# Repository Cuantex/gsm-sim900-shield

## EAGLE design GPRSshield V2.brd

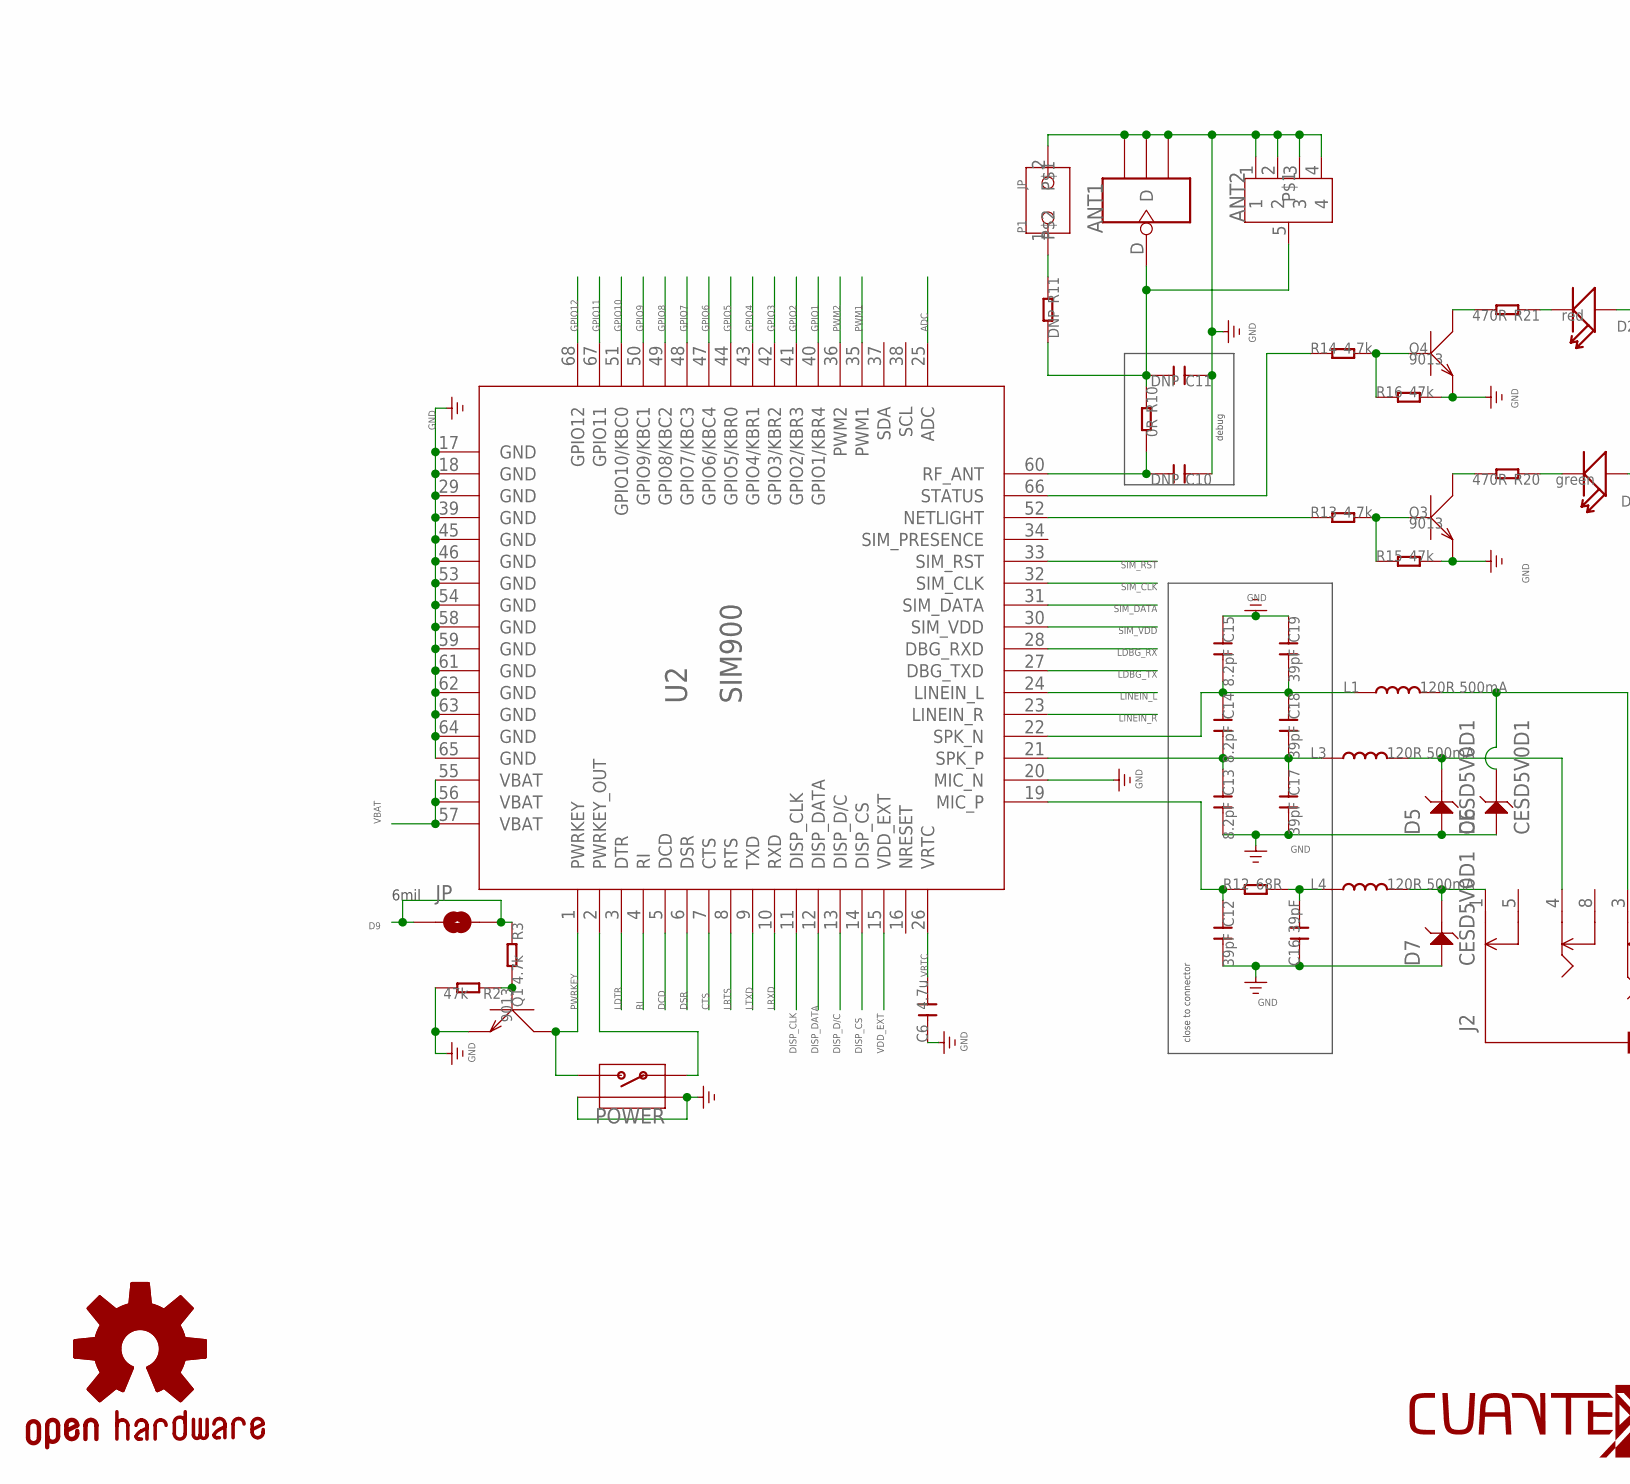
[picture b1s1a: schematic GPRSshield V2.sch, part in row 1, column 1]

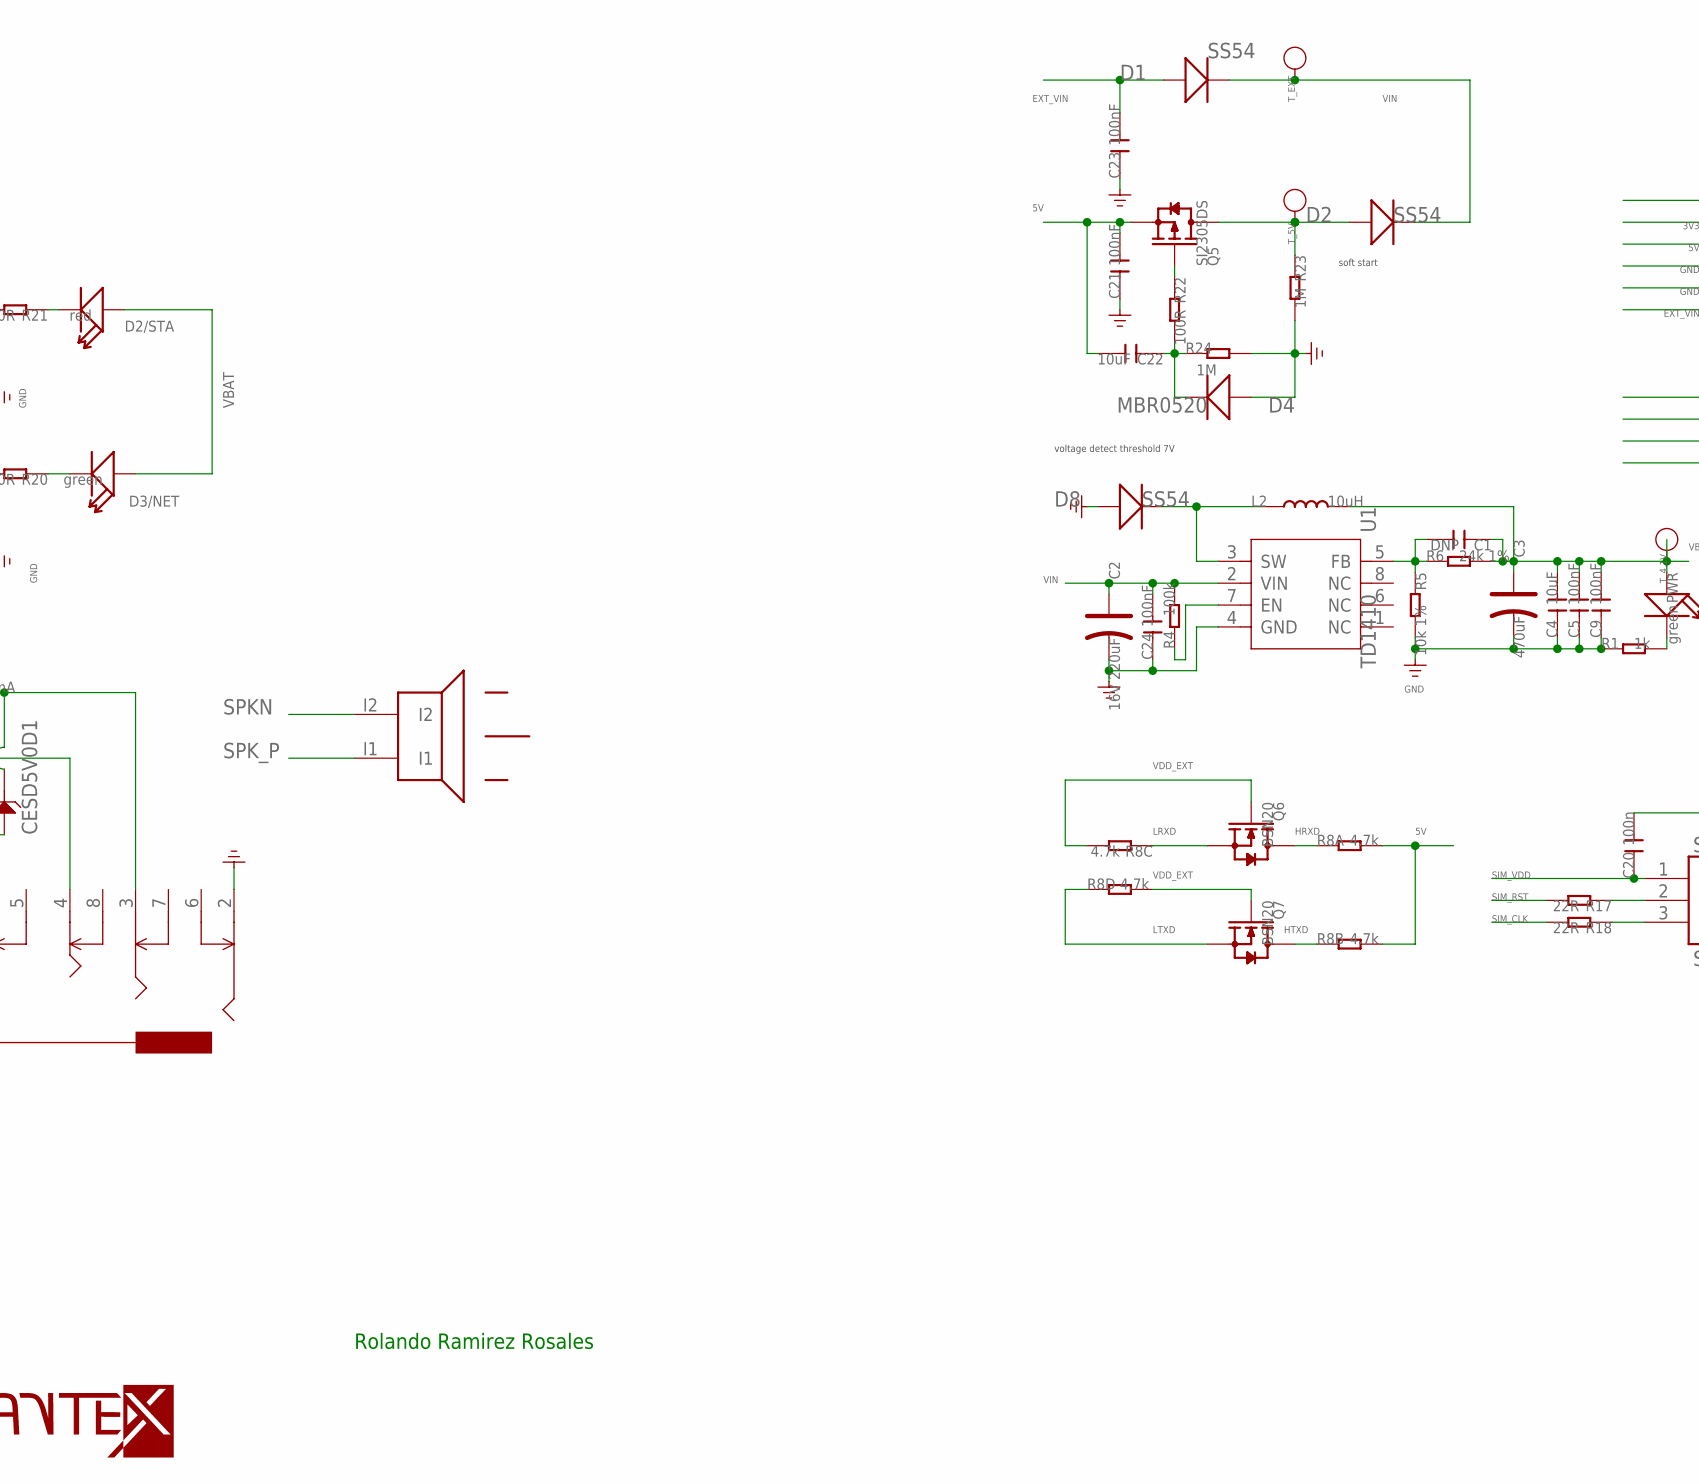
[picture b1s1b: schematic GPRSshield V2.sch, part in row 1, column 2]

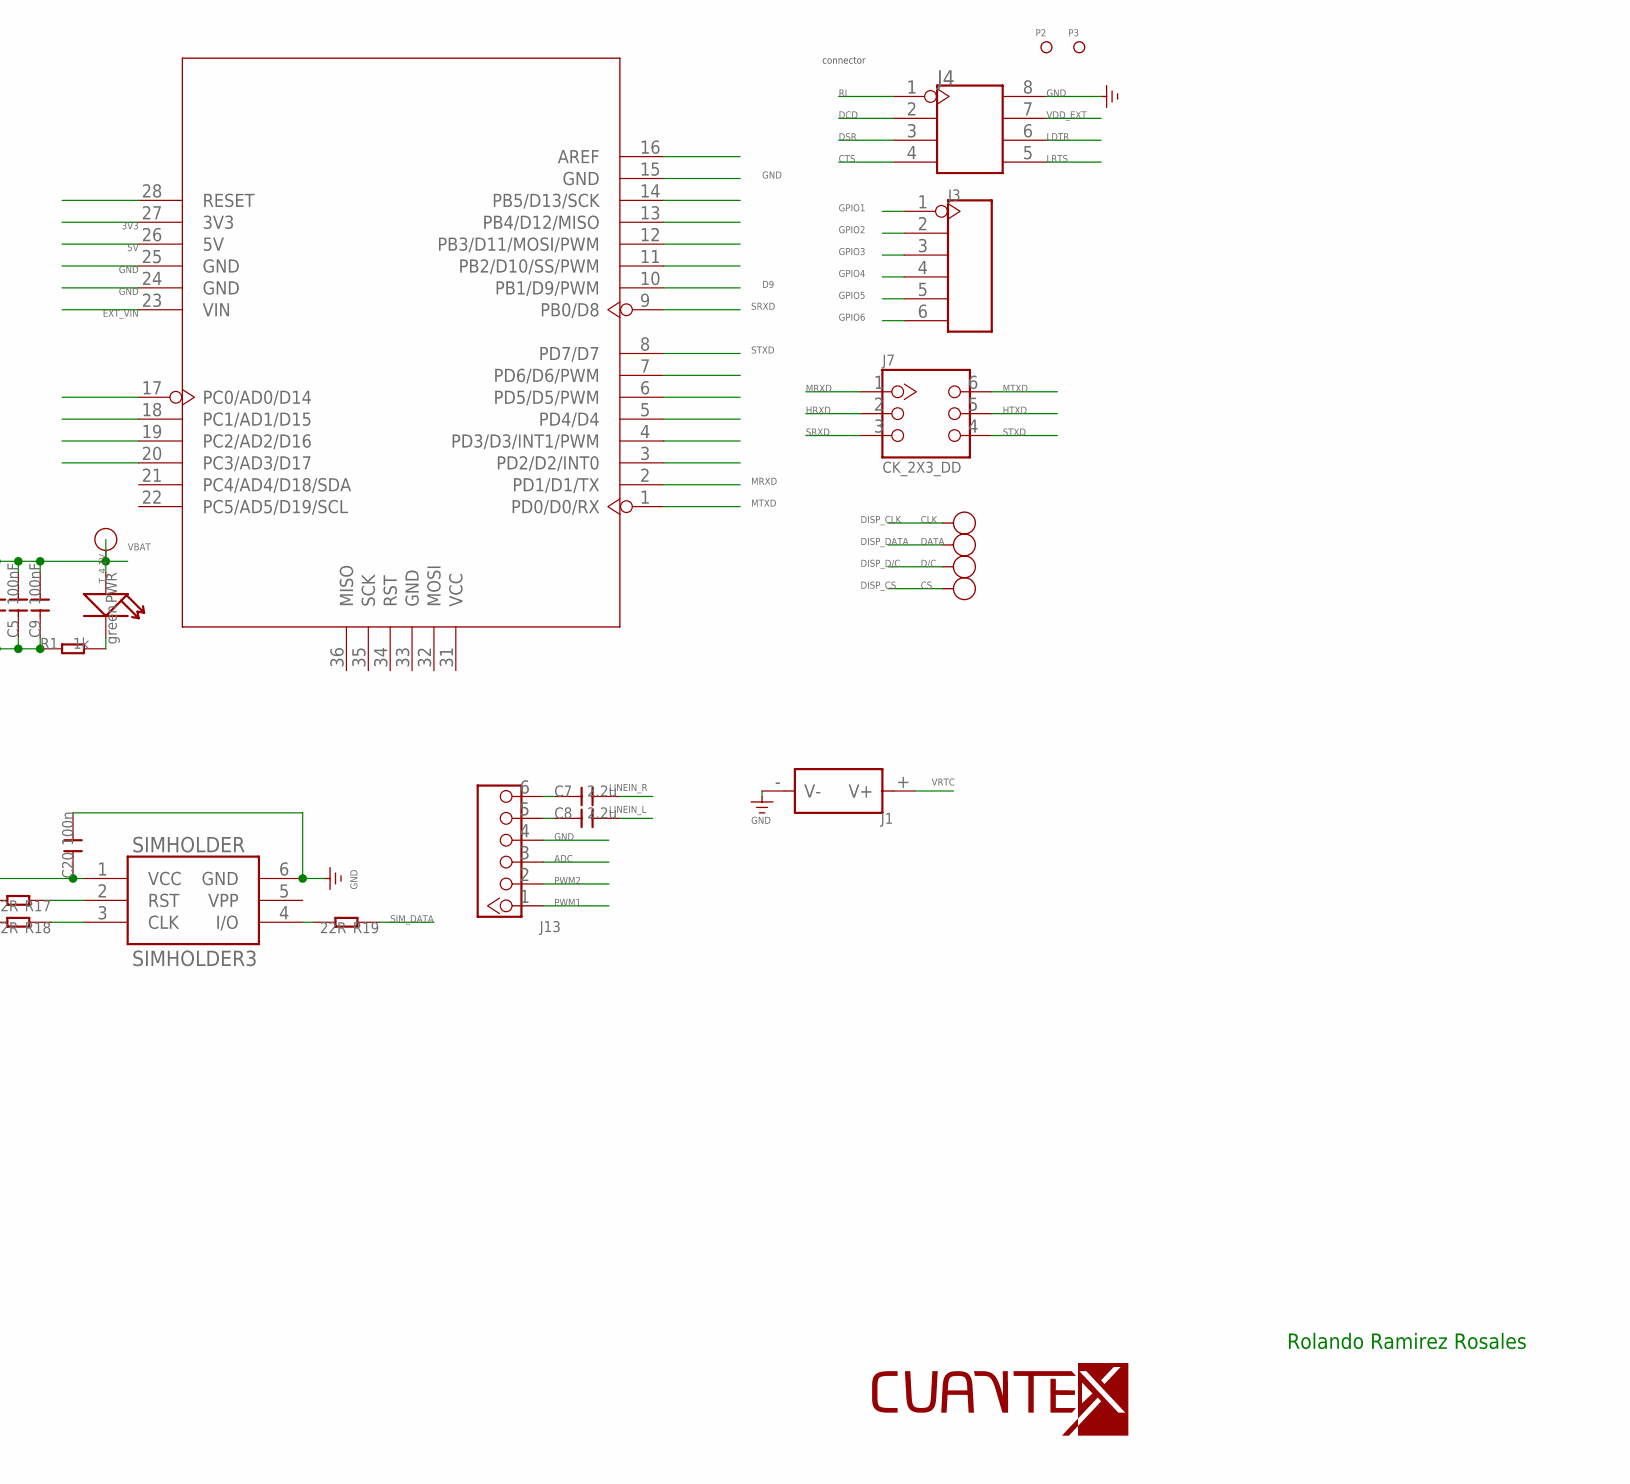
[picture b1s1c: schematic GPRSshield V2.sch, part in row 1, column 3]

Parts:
ANT1: ANTENNA-U-FL; 4P-U-FL
ANT2: ANTENNA-SMA-IPX; SMA-TO-IPX
C1, C10, C11: DNP; C0603
C2: 16V 220uF; ELECTRO-SMD-D-5.6MM
C3: 470uF; AVX-D
C4, C22: 10uF; C0805
C5, C9, C21, C23, C24: 100nF; C0603
C6: 4.7u; C0805
C7, C8: 2.2u; C0805
C12, C16, C17, C18, C19: 39pF; C0603
C13, C14, C15: 8.2pF; C0603
C20: 100n; C0603
CLK: PAD-TEST-POINT-CIRCLE'4545'; TP_4545
CS: PAD-TEST-POINT-CIRCLE'4545'; TP_4545
D1, D2, D8: SS54; SMB
D2/STA: red; LED-0603
D3/NET: green; LED-0603
D4: MBR0520; SOD123-2.7X1.6
D5, D6, D7: CESD5V0D1; SOD123-2.7X1.6
D/C: PAD-TEST-POINT-CIRCLE'4545'; TP_4545
DATA: PAD-TEST-POINT-CIRCLE'4545'; TP_4545
GOLD_ORB_SM1: OSHWLOGO_GOLD_ORB_SM; OSHW2
J1: HOLDER-BAT; SMD-CR1220-2
J2: AUDIO-8P'PJ-3536-L6S'; 8P-3.5-SMD
J3: HEADER-6P-65/35MIL; 6P-2.54-65/35MIL
J4: HEADER-2X4P-2.54; 2X4P-2.54
J7: CK_2X3_DD; CK_2X3
J13: HEADER_1X6; CK_1X6
JP: PAD-SOLDERJUMPERNC; 2P-SMD-3.3X2
L1, L3, L4: 120R 500mA; L0603
L2: 10uH; L0630
P1: JP
P2, P3: PAD-MARK; ROUND-MARK-1.0
POWER: BUTTON-4P-REINFORCE'TS-118E'; 4P-SMD-7X3.5X3.5H
PWR: green; D0603
Q1, Q3, Q4: 9013; SOT23
Q5: SI2305DS; SOT23
Q6, Q7: BSN20; SOT23
R1: 1k; R0603
R2, R15, R16: 47k; R0603
R3, R13, R14: 4.7k; R0603
R4: 100k; R0603
R5: 10k 1%; R0603
R6: 24k 1%; R0603
R8: 4.7k; 1206-8-3.3X2.4
R10: 0R; R0603
R11: DNP; R0603
R12: 68R; R0603
R17, R18, R19: 22R; R0603
R20, R21: 470R; R0603
R22: 100R; R0603
R23, R24: 1M; R0603
SIMHOLDER: SIMHOLDER3
T_4.1V, T_5V: PAD-TEST-POINT-CIRCLE'4545'; TP_4545; PARTNO DNP
T_EXT: PAD-TEST-POINT-CIRCLE'4545'; TP_4545; PARTNO DNP
U1: TD1410; SOP8
U2: SIM900
U3: ARDUINO'W/O-SILK'; ARDUINO-W/O-SILK
U$4: SPEAKER_HETPRO; SPK_SMD
U$11: LOGO-TOP-10MM; C-000
U$23: LOGO-TOP-30MM; C-1

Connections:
3V3: U3.27 (3V3)
5V: C21.2, C22.2, Q5.2 (S), R8.7 (2), R8.8 (2), U3.26 (5V)
ADC: J13.3, U2.25 (ADC)
CTS: J4.4, U2.7 (CTS)
D9: JP.1, JP.2, R3.1, U3.10 (PB1/D9/PWM)
DCD: J4.2, U2.5 (DCD)
DISP_CLK: CLK.T, U2.11 (DISP_CLK)
DISP_CS: CS.T, U2.14 (DISP_CS)
DISP_D/C: D/C.T, U2.13 (DISP_D/C)
DISP_DATA: DATA.T, U2.12 (DISP_DATA)
DSR: J4.3, U2.6 (DSR)
EXT_VIN: C23.2, D1.+, U3.23 (VIN)
GND: ANT1.GND1, ANT1.GND2, ANT1.GND3, ANT2.1, ANT2.2, ANT2.3, ANT2.4, C2.-, C3.-, C4.1, C5.1, C6.1, C9.1, C10.1, C11.1, C12.2, C13.2, C15.1, C16.1, C17.2, C19.1, C20.2, C21.1, C23.1, C24.1, D4.1 (+), D5.1, D6.1, D7.1, D8.+, J1.- (V-), J2.2, J4.8, J13.4, P1.2, POWER.S1, POWER.S2, Q1.2 (E), Q3.2 (E), Q4.2 (E), R1.1, R2.2, R5.2, R15.2, R16.2, R23.2, R24.2, SIMHOLDER.6 (GND), U1.4 (GND), U2.17 (GND), U2.18 (GND), U2.20 (MIC_N), U2.29 (GND), U2.39 (GND), U2.45 (GND), U2.46 (GND), U2.53 (GND), U2.54 (GND), U2.58 (GND), U2.59 (GND), U2.61 (GND), U2.62 (GND), U2.63 (GND), U2.64 (GND), U2.65 (GND), U3.15 (GND), U3.24 (GND), U3.25 (GND)
GPIO1: J3.1, U2.40 (GPIO1/KBR4)
GPIO2: J3.2, U2.41 (GPIO2/KBR3)
GPIO3: J3.3, U2.42 (GPIO3/KBR2)
GPIO4: J3.4, U2.43 (GPIO4/KBR1)
GPIO5: J3.5, U2.44 (GPIO5/KBR0)
GPIO6: J3.6, U2.47 (GPIO6/KBC4)
GPIO7: U2.48 (GPIO7/KBC3)
GPIO8: U2.49 (GPIO8/KBC2)
GPIO9: U2.50 (GPIO9/KBC1)
GPIO10: U2.51 (GPIO10/KBC0)
GPIO11: U2.67 (GPIO11)
GPIO12: U2.68 (GPIO12)
HRXD: J7.2, Q6.3 (D), R8.1
HTXD: J7.5, Q7.3 (D), R8.2 (1)
LDBG_RX: U2.28 (DBG_RXD)
LDBG_TX: U2.27 (DBG_TXD)
LDTR: J4.6, U2.3 (DTR)
LINEIN_L: C8.2, U2.24 (LINEIN_L)
LINEIN_R: C7.2, U2.23 (LINEIN_R)
LRTS: J4.5, U2.8 (RTS)
LRXD: Q6.2 (S), R8.3 (1), U2.10 (RXD)
LTXD: Q7.2 (S), R8.4 (1), U2.9 (TXD)
MRXD: J7.1, U3.2 (PD1/D1/TX)
MTXD: J7.6, U3.1 (PD0/D0/RX)
unnamed: C10.2, R10.2, U2.60 (RF_ANT)
unnamed: Q3.3 (C), R20.2
unnamed: R19.2, SIMHOLDER.4 (I/O)
unnamed: R18.1, SIMHOLDER.3 (CLK)
unnamed: R17.1, SIMHOLDER.2 (RST)
unnamed: D3/NET.-, R20.1
unnamed: Q3.1 (B), R13.2, R15.1
unnamed: PWR.-, R1.2
unnamed: R13.1, U2.52 (NETLIGHT)
unnamed: POWER.1, U2.2 (PWRKEY_OUT)
unnamed: R4.1, U1.7 (EN)
unnamed: C12.1, R12.1, U2.19 (MIC_P)
unnamed: C13.1, C14.2, C17.1, C18.2, L3.1, U2.21 (SPK_P)
unnamed: Q4.3 (C), R21.2
unnamed: D2/STA.-, R21.1
unnamed: Q4.1 (B), R14.2, R16.1
unnamed: C14.1, C15.2, C18.1, C19.2, L1.1, U2.22 (SPK_N)
unnamed: R14.1, U2.66 (STATUS)
unnamed: ANT1.D, ANT2.5, C11.2, R10.1, R11.2
unnamed: C7.1, J13.6
unnamed: C8.1, J13.5
unnamed: C16.2, L4.1, R12.2
unnamed: Q5.1 (G), R22.1
unnamed: Q1.1 (B), R2.1, R3.2
unnamed: C22.1, D4.2 (-), R22.2, R24.1
unnamed: D7.2, J2.1, L4.2
unnamed: C1.2, R5.1, R6.1, U1.5 (FB)
unnamed: P1.1, R11.1
PU2: D8.-, L2.1, U1.3 (SW)
PWM1: J13.1, U2.35 (PWM1)
PWM2: J13.2, U2.36 (PWM2)
PWRKEY: POWER.2, Q1.3 (C), U2.1 (PWRKEY)
RI: J4.1, U2.4 (RI)
SIM_CLK: R18.2, U2.32 (SIM_CLK)
SIM_DATA: R19.1, U2.31 (SIM_DATA)
SIM_RST: R17.2, U2.33 (SIM_RST)
SIM_VDD: C20.1, SIMHOLDER.1 (VCC), U2.30 (SIM_VDD)
SPKN: D6.2, J2.3, L1.2, U$4.I2
SPK_P: D5.2, J2.4, L3.2, U$4.I1
SRXD: J7.3, U3.9 (PB0/D8)
STXD: J7.4, U3.8 (PD7/D7)
TRP1: D2.+, Q5.3 (D), R23.1, T_5V.T
VBAT: C1.1, C3.+, C4.2, C5.2, C9.2, D2/STA.+, D3/NET.+, L2.2, PWR.+, R6.2, T_4.1V.T, U2.55 (VBAT), U2.56 (VBAT), U2.57 (VBAT)
VDD_EXT: J4.7, Q6.1 (G), Q7.1 (G), R8.5 (2), R8.6 (2), U2.15 (VDD_EXT)
VIN: C2.+, C24.2, D1.-, D2.-, R4.2, T_EXT.T, U1.2 (VIN)
VRTC: C6.2, J1.+ (V+), U2.26 (VRTC)

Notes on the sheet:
close to connector
debug
soft start
voltage detect threshold 7V
connector
6mil
Rolando Ramirez Rosales

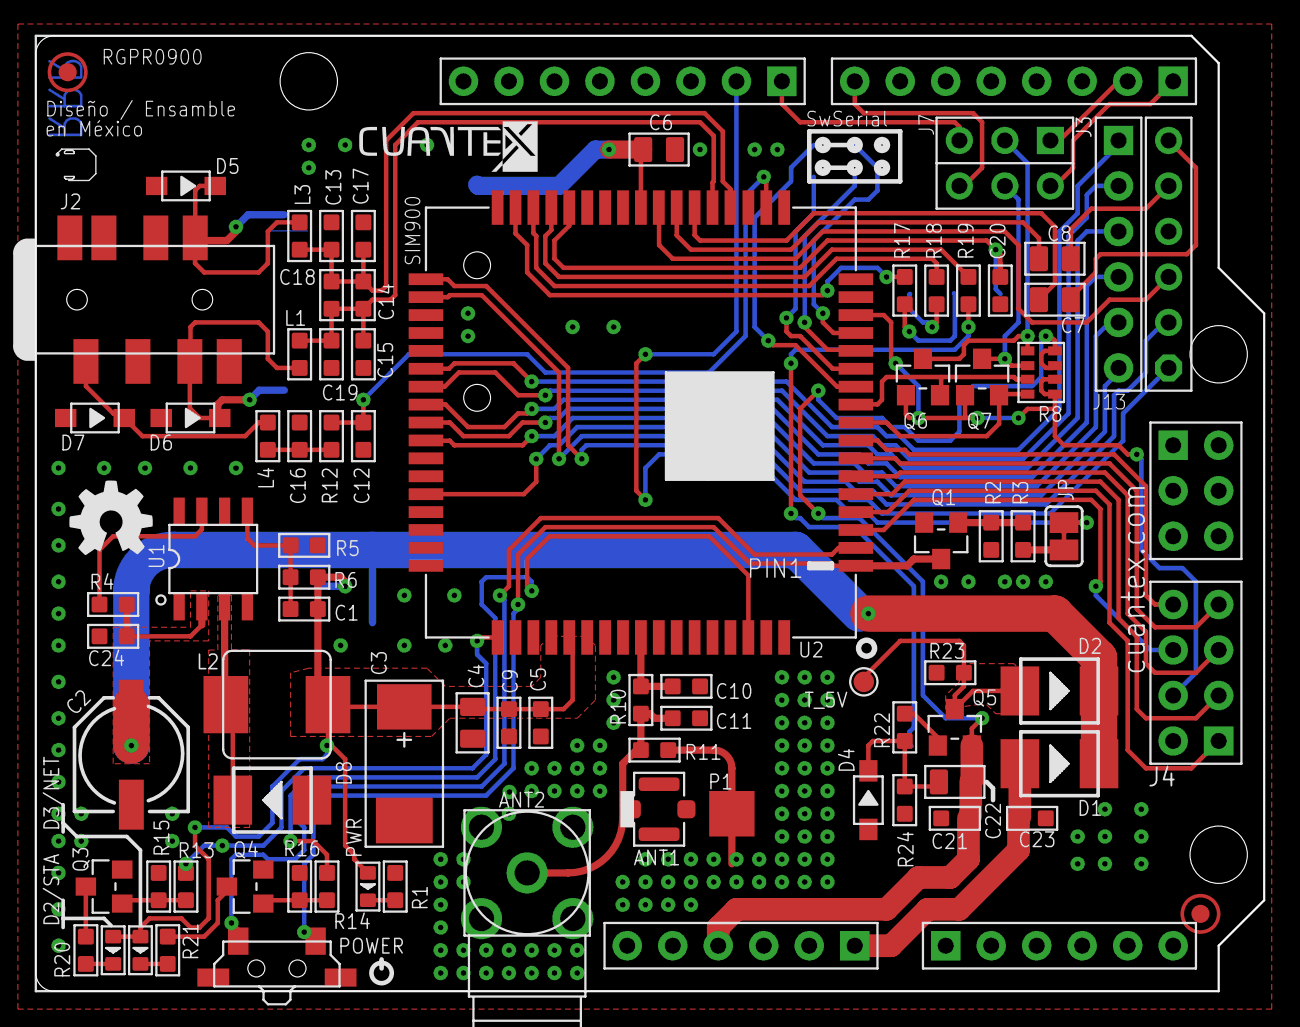
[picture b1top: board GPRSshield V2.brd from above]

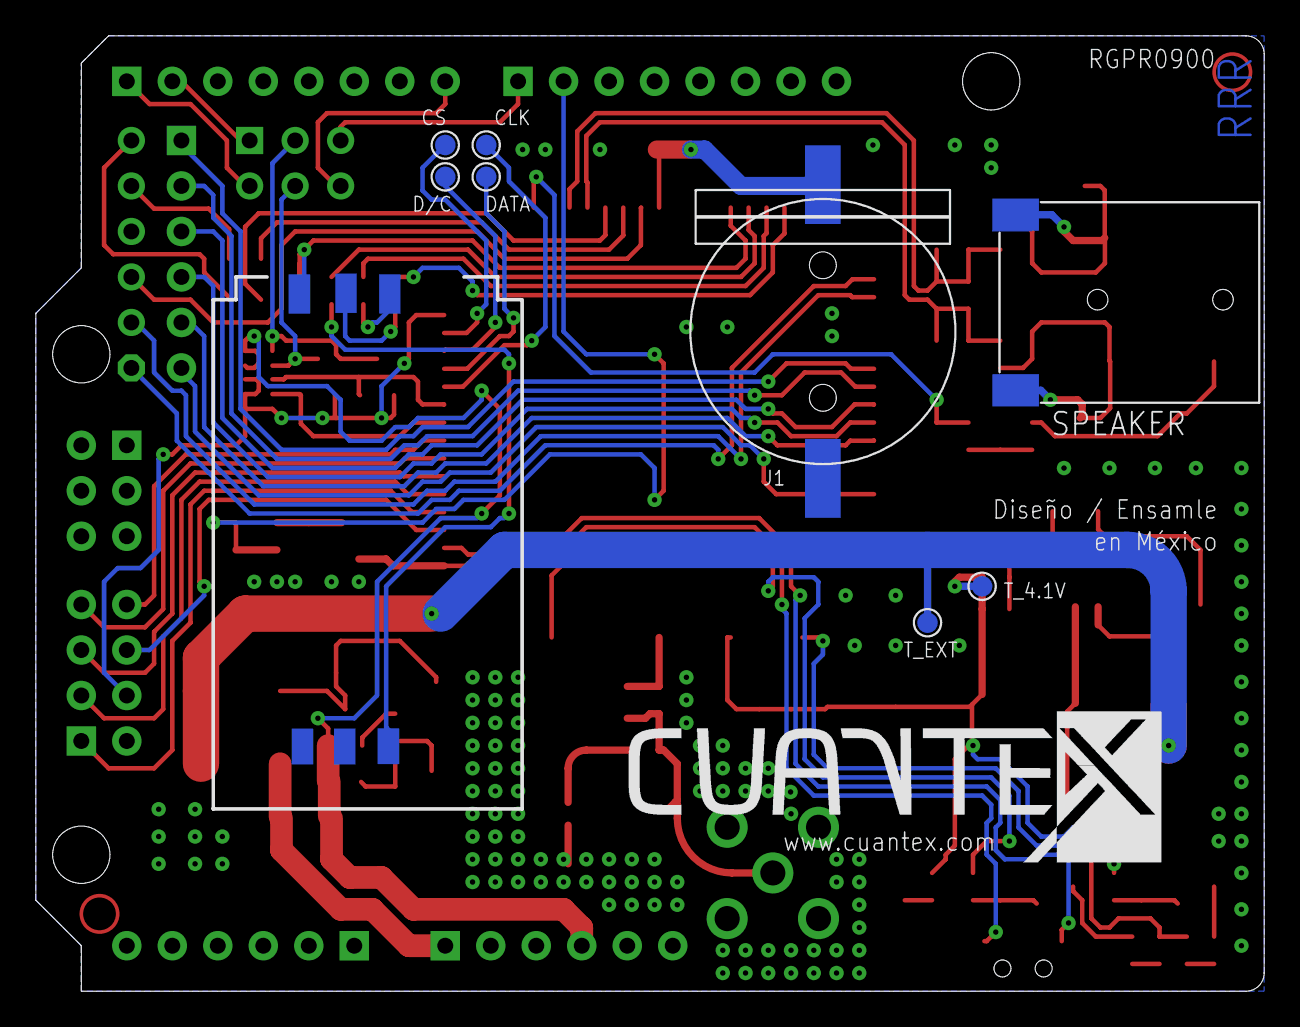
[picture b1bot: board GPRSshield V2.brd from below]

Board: 2 copper layers, 68.6 x 53.3 mm, 94 parts (10 on the bottom side), 74 nets.

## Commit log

2016-03-28 Archivos en Git
